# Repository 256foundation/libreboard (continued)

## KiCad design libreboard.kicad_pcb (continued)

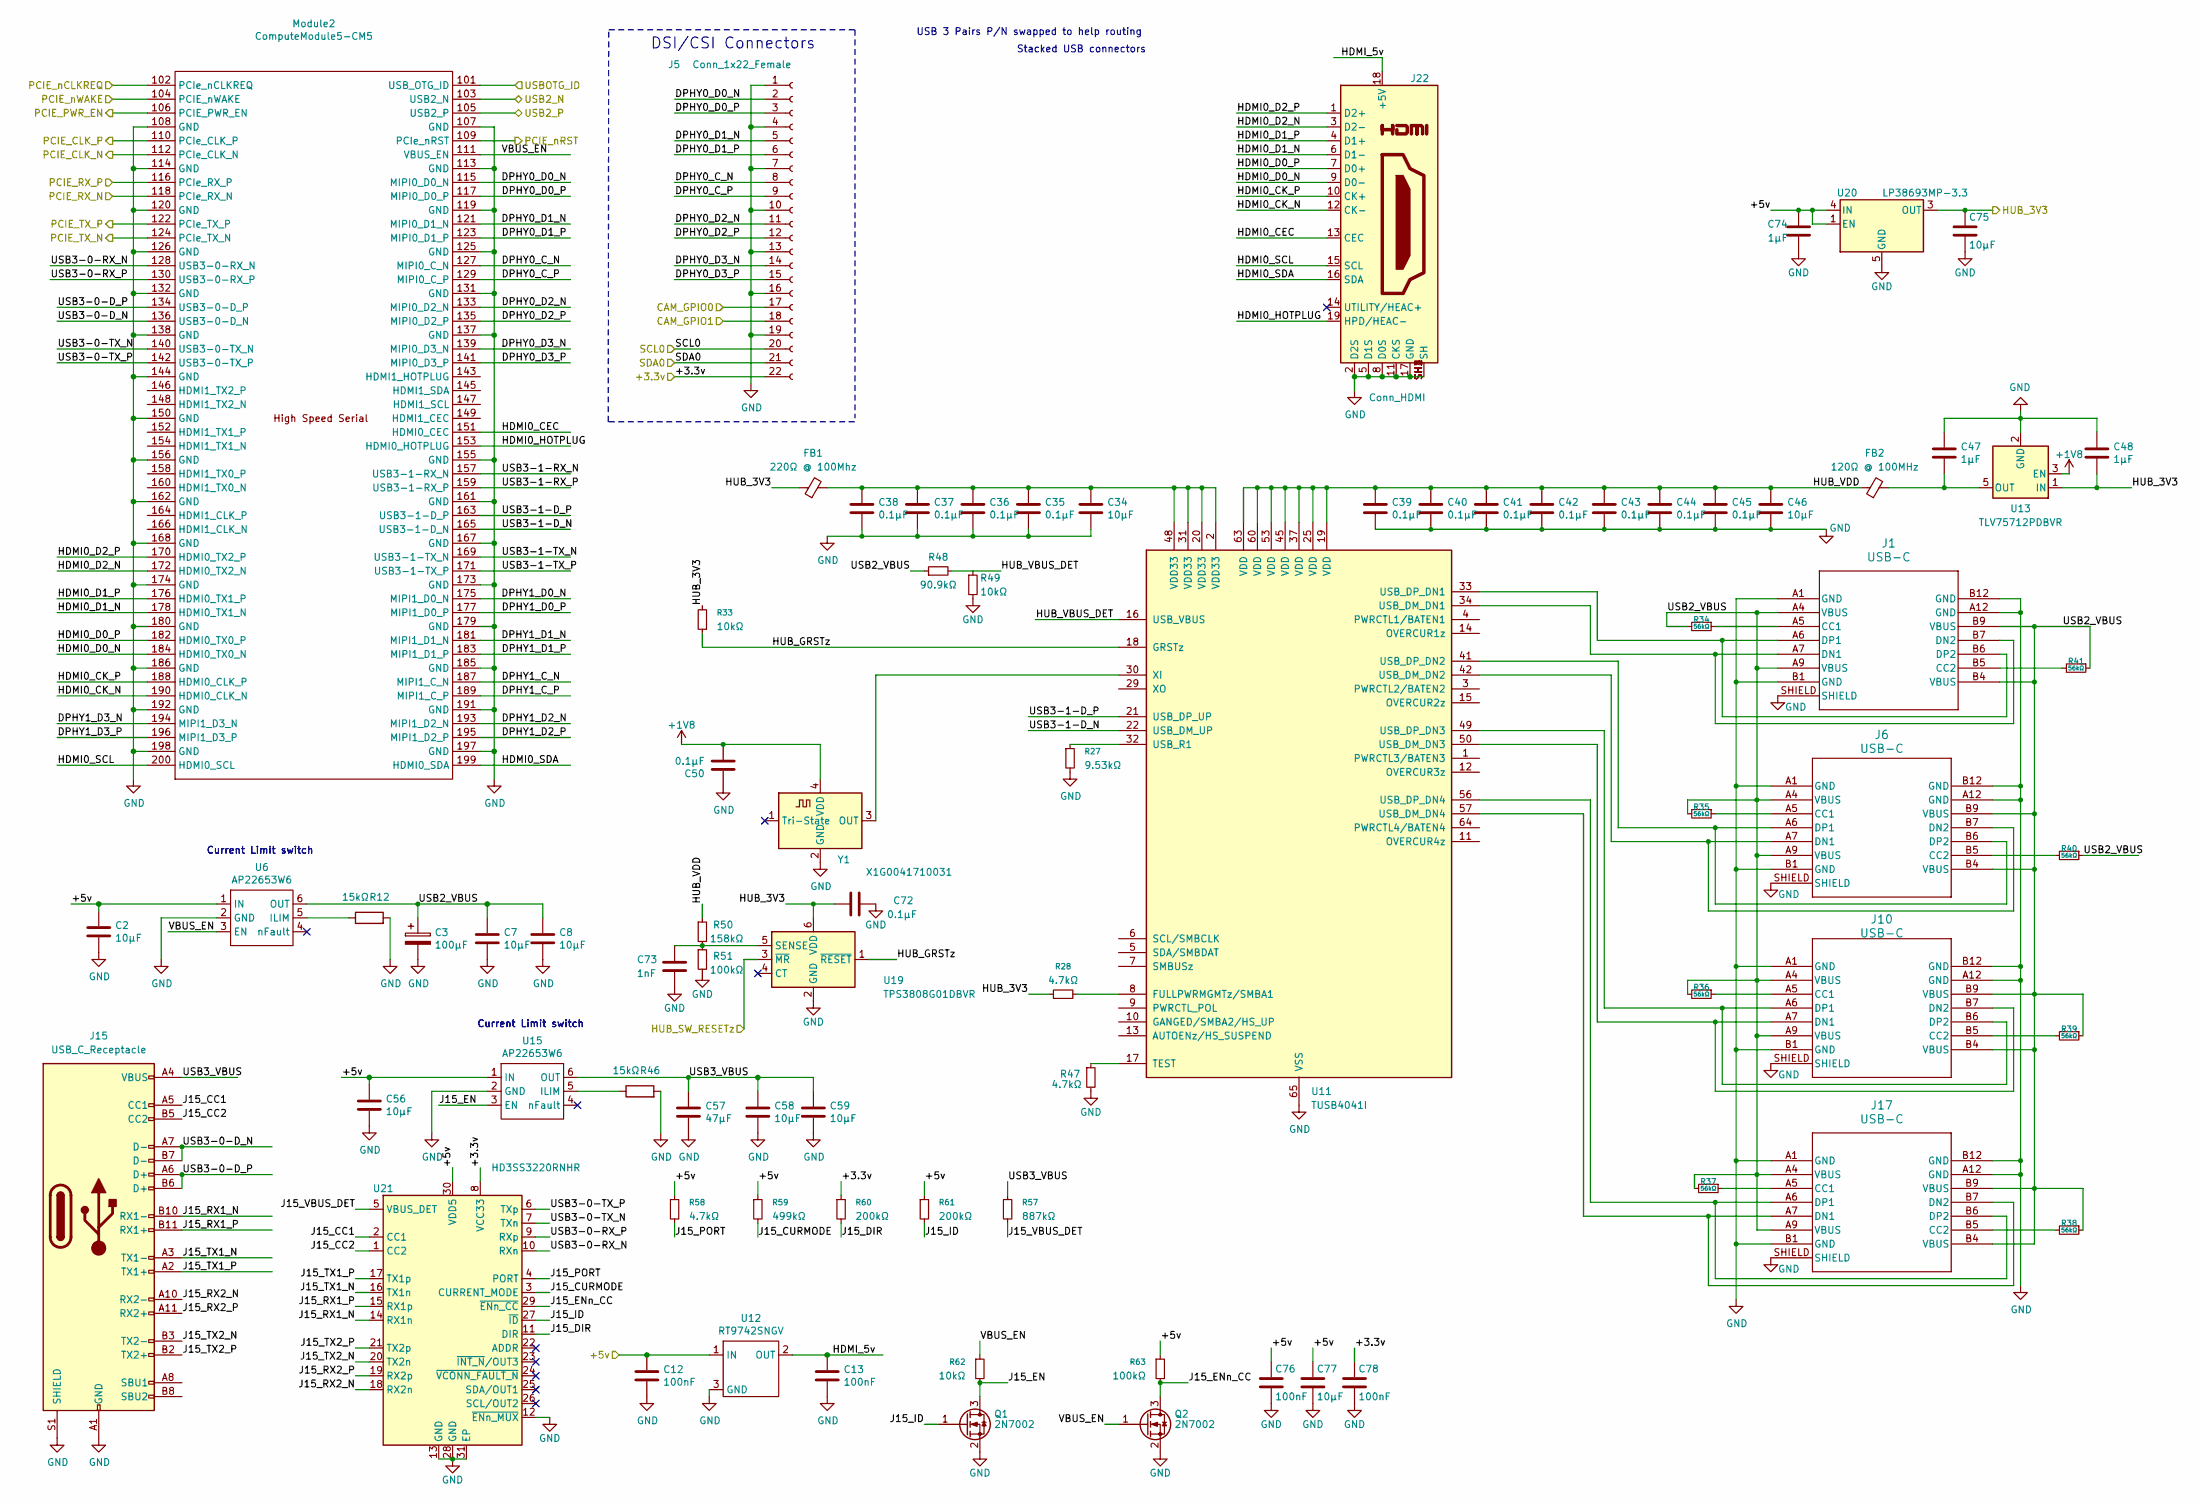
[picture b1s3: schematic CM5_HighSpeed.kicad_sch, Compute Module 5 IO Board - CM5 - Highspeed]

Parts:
C2, C7, C8, C56, C58, C59, C75, C77: 10µF; C_0805_2012Metric; Part Description Capacitor, Ceramic, 10µF, ±10%, 10V, X5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; LCSC C15850
C3: 100µF; CP_EIA-7343-31_Kemet-D; Part Description Capacitor, Aluminum, 100µF, ±20%, 10V, 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; LCSC C3275146
C12, C13: 100nF; C_0402_1005Metric; Part Description Capacitor, Ceramic, 0.1µF, ±10%, 6.3V, 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; LCSC C1525
C34, C46: 10µF; C_0402_1005Metric; Part Description Capacitor, Ceramic, 10µF, ±20%, 6.3V, X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; LCSC C15525
C35, C36, C37, C38, C39, C40, C41, C42, C43, C44, C45, C50: 0.1µF; C_0402_1005Metric; Part Description Capacitor, Ceramic, 0.1µF, ±10%, 6.3V, 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; LCSC C1525
C47, C48: 1µF; C_0402_1005Metric; Part Description Capacitor, Ceramic, 1µF, ±10%, 6.3V, X5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; LCSC C52923
C57: 47µF; C_1206_3216Metric; Part Description 47 µF ±20% 10V Ceramic Capacitor X5R 12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; LCSC C96123
C72: 0.1µF; C_0603_1608Metric; Part Description CAP CER 0.1UF 50V X7R 0603; LCSC C14663
C73: 1nF; C_0603_1608Metric; Part Description Capacitor, Ceramic, 1nF, ±5%, 50V, C0G,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; LCSC C77026
C74: 1µF; C_0402_1005Metric; Part Description 1 µF ±10% 50V Ceramic Capacitor X5R 040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; LCSC C1518208
C76, C78: 100nF; C_0402_1005Metric; Part Description CAP CER 0.1UF 50V X7R 0402; LCSC C307331
FB1: 220Ω @ 100Mhz; BEADC1005X55N; Part Description Filter, Ferrite Bead, 220Ω @ 100MHz, SM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; LCSC C85813
FB2: 120Ω @ 100MHz; L_0603_1608Metric; Part Description Filter, Ferrite Bead, 120Ω @ 100MHz, 3A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; LCSC C85831
J1, J6, J10, J17: USB-C; 216989-0001_MOL; Part Description Receptacle, USB-C, 2.0, 24 pin (14+10 D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; LCSC C3197955
J5: Conn_1x22_Female; Hirose_FH12-22S-0.5SH_1x22-1MP_P0.50mm_Horizontal; Part Description Connector, 22 Position FFC, FPC Connect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; LCSC C597981
J15: USB_C_Receptacle; USB_C_Receptacle_Molex_105450-0101; Part Description Connector, USB-C 3.2 Gen 2; LCSC C134092
J22: Conn_HDMI; EDAC 690-019-298-412; Part Description Connector, HDMI Type A, Female, Right A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; LCSC C5291558
Module2: ComputeModule5-CM5; CM5_Connector_B; Part Description Connector, CM Receptacle, 100 pin, 0.4m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; LCSC C6782225
Q1, Q2: 2N7002; SOT-23; Part Description MOSFET, N-channel, 60V, 115mA, SOT-23; LCSC C8545
R12, R46: 15kΩ; R_0402_1005Metric; Part Description Resistor, 15kΩ, ±1%, 0.1W, SMD 0402 (10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; LCSC C25756
R27: 9.53kΩ; R_0402_1005Metric; Part Description Resistor, 9.53kΩ, ±1%, 0.1W, SMD 0402 (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; LCSC C409938
R28, R58: 4.7kΩ; R_0402_1005Metric; Part Description Resistor, 4.7kΩ, ±1%, 0.1W, SMD 0402 (1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; LCSC C25900
R33, R62: 10kΩ; R_0402_1005Metric; Part Description Resistor, 10kΩ, ±1%, 0.1W, SMD 0402 (10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; LCSC C25744
R34, R35, R36, R37, R38, R39, R40, R41: 56kΩ; R_0402_1005Metric; Part Description Resistor, 56kΩ, ±1%, 0.1W, SMD 0402 (10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; LCSC C25796
R47: 4.7kΩ; R_0603_1608Metric; Part Description Resistor, 4.7kΩ, ±1%, 0.1W, SMD 0603 (1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; LCSC C23162
R48: 90.9kΩ; R_0603_1608Metric; Part Description Resistor, 90.9kΩ, ±1%, 0.1W, SMD 0603 (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; LCSC C403390
R49: 10kΩ; R_0603_1608Metric; Part Description Resistor, 10kΩ, ±1%, 0.1W, SMD 0603 (16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; LCSC C25804
R50: 158kΩ; R_0603_1608Metric; Part Description Resistor, 158kΩ, ±1%, 0.1W, SMD 0603 (1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; LCSC C22883
R51: 100kΩ; R_0603_1608Metric; Part Description Resistor, 100kΩ, ±1%, 0.1W, SMD 0603 (1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; LCSC C25803
R57: 887kΩ; R_0402_1005Metric; Part Description Resistor, 887kΩ, ±1%, 0.1W, SMD 0402 (1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; LCSC C409935
R59: 499kΩ; R_0402_1005Metric; Part Description Resistor, 499kΩ, ±1%, 0.1W, SMD 0402 (1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; LCSC C2986233
R60, R61: 200kΩ; R_0402_1005Metric; Part Description Resistor, 200kΩ, ±1%, 0.1W, SMD 0402 (1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; LCSC C25764
R63: 100kΩ; R_0402_1005Metric; Part Description Resistor, 100kΩ, ±1%, 0.1W, SMD 0402 (1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; LCSC C25741
U6, U15: AP22653W6; SOT-23-6; Part Description Power Switch/Driver, 1:1, P-Channel, 2.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; LCSC C2158037
U11: TUSB4041I; Texas_TQFP-64-1EP_10x10mm_P0.5mm_EP8x8mm_Mask4.44x4.44mm_Th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; Part Description Controller, USB Hub, 64-HTQFP; LCSC C192089
U12: RT9742SNGV; TSOT-23_HandSoldering; Part Description Power Switch/Driver, 1:1, N-Channel, 50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; LCSC C3235509
U13: TLV75712PDBVR; SOT-23-5; Part Description LDO, fixed 1.2 V, 1 A, SOT-23-5; LCSC C1509296
U19: TPS3808G01DBVR; SOT-23-6; Part Description Voltage supervisor, adjustable (0.405 V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; LCSC C19653
U20: LP38693MP-3.3; SOT-223-5; Part Description IC, LDO, 3.3V, 500mA, SOT-223-5, enable; LCSC C130904
U21: HD3SS3220RNHR; Texas_RNH0030A_WQFN-30-1EP_2.5x4.5mm_P0.4mm_EP1.2x3.2mm_The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; Part Description IC, USB Type-C DRP port controller + US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; LCSC C165155
Y1: X1G0041710031; Oscillator_SMD_ECS_2520MV-xxx-xx-4Pin_2.5x2.0mm; Part Description Oscillator SG-210STF, 24MHz, CMOS, 1.6V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; LCSC C70559

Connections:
+1V8: C50.2, U13.3 (EN), Y1.4 (VDD); also elsewhere on the board
+5v: C2.1, C12.1, C56.1, C74.1, C76.1, C77.1, R58.1, R59.1, R61.1, R63.1, U6.1 (IN), U12.1 (IN), U15.1 (IN), U20.1 (EN), U20.4 (IN), U21.30 (VDD5); also elsewhere on the board
/+3.3v: C78.1, J5.22, R60.1, U21.8 (VCC33); also elsewhere on the board
/CM5_GPIO ( Ethernet, GPIO, SDCARD)/CAM_GPIO0: J5.17; also elsewhere on the board
/CM5_GPIO ( Ethernet, GPIO, SDCARD)/CAM_GPIO1: J5.18; also elsewhere on the board
/CM5_GPIO ( Ethernet, GPIO, SDCARD)/HUB_SW_RESETz: U19.3 (~MR); also elsewhere on the board
/CM5_GPIO ( Ethernet, GPIO, SDCARD)/SCL0: J5.20; also elsewhere on the board
/CM5_GPIO ( Ethernet, GPIO, SDCARD)/SDA0: J5.21; also elsewhere on the board
/CM5_GPIO ( Ethernet, GPIO, SDCARD)/USBOTG: Module2.101 (USB_OTG_ID); also elsewhere on the board
/CM5_HighSpeed/DPHY0_C_N: J5.8, Module2.127 (MIPI0_C_N)
/CM5_HighSpeed/DPHY0_C_P: J5.9, Module2.129 (MIPI0_C_P)
/CM5_HighSpeed/DPHY0_D0_N: J5.2, Module2.115 (MIPI0_D0_N)
/CM5_HighSpeed/DPHY0_D0_P: J5.3, Module2.117 (MIPI0_D0_P)
/CM5_HighSpeed/DPHY0_D1_N: J5.5, Module2.121 (MIPI0_D1_N)
/CM5_HighSpeed/DPHY0_D1_P: J5.6, Module2.123 (MIPI0_D1_P)
/CM5_HighSpeed/DPHY0_D2_N: J5.11, Module2.133 (MIPI0_D2_N)
/CM5_HighSpeed/DPHY0_D2_P: J5.12, Module2.135 (MIPI0_D2_P)
/CM5_HighSpeed/DPHY0_D3_N: J5.14, Module2.139 (MIPI0_D3_N)
/CM5_HighSpeed/DPHY0_D3_P: J5.15, Module2.141 (MIPI0_D3_P)
/CM5_HighSpeed/DPHY1_C_N: Module2.187 (MIPI1_C_N)
/CM5_HighSpeed/DPHY1_C_P: Module2.189 (MIPI1_C_P)
/CM5_HighSpeed/DPHY1_D0_N: Module2.175 (MIPI1_D0_N)
/CM5_HighSpeed/DPHY1_D0_P: Module2.177 (MIPI1_D0_P)
/CM5_HighSpeed/DPHY1_D1_N: Module2.181 (MIPI1_D1_N)
/CM5_HighSpeed/DPHY1_D1_P: Module2.183 (MIPI1_D1_P)
/CM5_HighSpeed/DPHY1_D2_N: Module2.193 (MIPI1_D2_N)
/CM5_HighSpeed/DPHY1_D2_P: Module2.195 (MIPI1_D2_P)
/CM5_HighSpeed/DPHY1_D3_N: Module2.194 (MIPI1_D3_N)
/CM5_HighSpeed/DPHY1_D3_P: Module2.196 (MIPI1_D3_P)
/CM5_HighSpeed/HDMI0_CEC: J22.13 (CEC), Module2.151 (HDMI0_CEC)
/CM5_HighSpeed/HDMI0_CK_N: J22.12 (CK-), Module2.190 (HDMI0_CLK_N)
/CM5_HighSpeed/HDMI0_CK_P: J22.10 (CK+), Module2.188 (HDMI0_CLK_P)
/CM5_HighSpeed/HDMI0_D0_N: J22.9 (D0-), Module2.184 (HDMI0_TX0_N)
/CM5_HighSpeed/HDMI0_D0_P: J22.7 (D0+), Module2.182 (HDMI0_TX0_P)
/CM5_HighSpeed/HDMI0_D1_N: J22.6 (D1-), Module2.178 (HDMI0_TX1_N)
/CM5_HighSpeed/HDMI0_D1_P: J22.4 (D1+), Module2.176 (HDMI0_TX1_P)
/CM5_HighSpeed/HDMI0_D2_N: J22.3 (D2-), Module2.172 (HDMI0_TX2_N)
/CM5_HighSpeed/HDMI0_D2_P: J22.1 (D2+), Module2.170 (HDMI0_TX2_P)
/CM5_HighSpeed/HDMI0_HOTPLUG: J22.19 (HPD/HEAC-), Module2.153 (HDMI0_HOTPLUG)
/CM5_HighSpeed/HDMI0_SCL: J22.15 (SCL), Module2.200 (HDMI0_SCL)
/CM5_HighSpeed/HDMI0_SDA: J22.16 (SDA), Module2.199 (HDMI0_SDA)
/CM5_HighSpeed/HDMI_5v: C13.1, J22.18 (+5V), U12.2 (OUT)
/CM5_HighSpeed/HUB_GRSTz: R33.1, U11.18 (GRSTz), U19.1 (~RESET)
/CM5_HighSpeed/HUB_VBUS_DET: R48.2, R49.1, U11.16 (USB_VBUS)
/CM5_HighSpeed/HUB_VDD: C39.1, C40.1, C41.1, C42.1, C43.1, C44.1, C45.1, C46.1, FB2.1, R50.1, U11.19 (VDD), U11.25 (VDD), U11.37 (VDD), U11.45 (VDD), U11.53 (VDD), U11.60 (VDD), U11.63 (VDD)
/CM5_HighSpeed/J15_CC1: J15.A5 (CC1), U21.2 (CC1)
/CM5_HighSpeed/J15_CC2: J15.B5 (CC2), U21.1 (CC2)
/CM5_HighSpeed/J15_CURMODE: R59.2, U21.3 (CURRENT_MODE)
/CM5_HighSpeed/J15_DIR: R60.2, U21.11 (DIR)
/CM5_HighSpeed/J15_EN: Q1.3 (D), R62.2, U15.3 (EN)
/CM5_HighSpeed/J15_ENn_CC: Q2.3 (D), R63.2, U21.29 (~ENn_CC)
/CM5_HighSpeed/J15_ID: Q1.1 (G), R61.2, U21.27 (~ID)
/CM5_HighSpeed/J15_PORT: R58.2, U21.4 (PORT)
/CM5_HighSpeed/J15_RX1_N: J15.B10 (RX1-), U21.14 (RX1n)
/CM5_HighSpeed/J15_RX1_P: J15.B11 (RX1+), U21.15 (RX1p)
/CM5_HighSpeed/J15_RX2_N: J15.A10 (RX2-), U21.18 (RX2n)
/CM5_HighSpeed/J15_RX2_P: J15.A11 (RX2+), U21.19 (RX2p)
/CM5_HighSpeed/J15_TX1_N: J15.A3 (TX1-), U21.16 (TX1n)
/CM5_HighSpeed/J15_TX1_P: J15.A2 (TX1+), U21.17 (TX1p)
/CM5_HighSpeed/J15_TX2_N: J15.B3 (TX2-), U21.20 (TX2n)
/CM5_HighSpeed/J15_TX2_P: J15.B2 (TX2+), U21.21 (TX2p)
/CM5_HighSpeed/J15_VBUS_DET: R57.2, U21.5 (VBUS_DET)
/CM5_HighSpeed/PCIE_CLK_N: Module2.112 (PCIe_CLK_N); also elsewhere on the board
/CM5_HighSpeed/PCIE_CLK_P: Module2.110 (PCIe_CLK_P); also elsewhere on the board
/CM5_HighSpeed/PCIE_PWR_EN: Module2.106 (PCIE_PWR_EN); also elsewhere on the board
/CM5_HighSpeed/PCIE_RX_N: Module2.118 (PCIe_RX_N); also elsewhere on the board
/CM5_HighSpeed/PCIE_RX_P: Module2.116 (PCIe_RX_P); also elsewhere on the board
/CM5_HighSpeed/PCIE_TX_N: Module2.124 (PCIe_TX_N); also elsewhere on the board
/CM5_HighSpeed/PCIE_TX_P: Module2.122 (PCIe_TX_P); also elsewhere on the board
/CM5_HighSpeed/PCIE_nCLKREQ: Module2.102 (PCIe_nCLKREQ); also elsewhere on the board
/CM5_HighSpeed/PCIE_nRST: Module2.109 (PCIe_nRST); also elsewhere on the board
/CM5_HighSpeed/PCIE_nWAKE: Module2.104 (PCIE_nWAKE); also elsewhere on the board
/CM5_HighSpeed/USB2_VBUS: C3.1, C7.1, C8.1, J1.A4 (VBUS), J1.A9 (VBUS), J1.B4 (VBUS), J1.B9 (VBUS), J6.A4 (VBUS), J6.A9 (VBUS), J6.B4 (VBUS), J6.B9 (VBUS), J10.A4 (VBUS), J10.A9 (VBUS), J10.B4 (VBUS), J10.B9 (VBUS), J17.A4 (VBUS), J17.A9 (VBUS), J17.B4 (VBUS), J17.B9 (VBUS), R34.2, R35.2, R36.2, R37.2, R38.1, R39.1, R40.1, R41.1, R48.1, U6.6 (OUT)
/CM5_HighSpeed/USB3-0-D_N: J15.A7 (D-), J15.B7 (D-), Module2.136 (USB3-0-D_N)
/CM5_HighSpeed/USB3-0-D_P: J15.A6 (D+), J15.B6 (D+), Module2.134 (USB3-0-D_P)
/CM5_HighSpeed/USB3-0-RX_N: Module2.128 (USB3-0-RX_N), U21.10 (RXn)
/CM5_HighSpeed/USB3-0-RX_P: Module2.130 (USB3-0-RX_P), U21.9 (RXp)
/CM5_HighSpeed/USB3-0-TX_N: Module2.140 (USB3-0-TX_N), U21.7 (TXn)
/CM5_HighSpeed/USB3-0-TX_P: Module2.142 (USB3-0-TX_P), U21.6 (TXp)
/CM5_HighSpeed/USB3-1-D_N: Module2.165 (USB3-1-D_N), U11.22 (USB_DM_UP)
/CM5_HighSpeed/USB3-1-D_P: Module2.163 (USB3-1-D_P), U11.21 (USB_DP_UP)
/CM5_HighSpeed/USB3-1-RX_N: Module2.157 (USB3-1-RX_N)
/CM5_HighSpeed/USB3-1-RX_P: Module2.159 (USB3-1-RX_P)
/CM5_HighSpeed/USB3-1-TX_N: Module2.169 (USB3-1-TX_N)
/CM5_HighSpeed/USB3-1-TX_P: Module2.171 (USB3-1-TX_P)
/CM5_HighSpeed/USB3_VBUS: C57.1, C58.1, C59.1, J15.A4 (VBUS), J15.A9 (VBUS), J15.B4 (VBUS), J15.B9 (VBUS), R57.1, U15.6 (OUT)
/CM5_HighSpeed/VBUS_EN: Module2.111 (VBUS_EN), Q2.1 (G), R62.1, U6.3 (EN)
/HUB_3V3: C48.2, C72.1, C75.1, FB1.1, R28.1, R33.2, U13.1 (IN), U19.6 (VDD), U20.3 (OUT); also elsewhere on the board
/USB2_N: Module2.103 (USB2_N); also elsewhere on the board
/USB2_P: Module2.105 (USB2_P); also elsewhere on the board
GND: C2.2, C3.2, C7.2, C8.2, C12.2, C13.2, C34.2, C35.2, C36.2, C37.2, C38.2, C39.2, C40.2, C41.2, C42.2, C43.2, C44.2, C45.2, C46.2, C47.1, C48.1, C50.1, C56.2, C57.2, C58.2, C59.2, C72.2, C73.2, C74.2, C75.2, C76.2, C77.2, C78.2, J1.A1 (GND), J1.A12 (GND), J1.B1 (GND), J1.B12 (GND), J1.SHIELD, J5.1, J5.4, J5.7, J5.10, J5.13, J5.16, J5.19, J6.A1 (GND), J6.A12 (GND), J6.B1 (GND), J6.B12 (GND), J6.SHIELD, J10.A1 (GND), J10.A12 (GND), J10.B1 (GND), J10.B12 (GND), J10.SHIELD, J15.A1 (GND), J15.A12 (GND), J15.B1 (GND), J15.B12 (GND), J15.S1 (SHIELD), J17.A1 (GND), J17.A12 (GND), J17.B1 (GND), J17.B12 (GND), J17.SHIELD, J22.2 (D2S), J22.5 (D1S), J22.8 (D0S), J22.11 (CKS), J22.17 (GND), J22.SH1 (SH), J22.SH2 (SH), J22.SH3 (SH), J22.SH4 (SH), Module2.107 (GND), Module2.108 (GND), Module2.113 (GND), Module2.114 (GND), Module2.119 (GND), Module2.120 (GND), Module2.125 (GND), Module2.126 (GND), Module2.131 (GND), Module2.132 (GND), Module2.137 (GND), Module2.138 (GND), Module2.144 (GND), Module2.150 (GND), Module2.155 (GND), Module2.156 (GND), Module2.161 (GND), Module2.162 (GND), Module2.167 (GND), Module2.168 (GND), Module2.173 (GND), Module2.174 (GND), Module2.179 (GND), Module2.180 (GND), Module2.185 (GND), Module2.186 (GND), Module2.191 (GND), Module2.192 (GND), Module2.197 (GND), Module2.198 (GND), Q1.2 (S), Q2.2 (S), R12.2, R27.2, R46.2, R47.2, R49.2, R51.2, U6.2 (GND), U11.65 (VSS), U12.3 (GND), U13.2 (GND), U15.2 (GND), U19.2 (GND), U20.5 (GND), U21.12 (~ENn_MUX), U21.13 (GND), U21.28 (GND), U21.31 (EP), Y1.2 (GND); also elsewhere on the board
unnamed: C34.1, C35.1, C36.1, C37.1, C38.1, FB1.2, U11.2 (VDD33), U11.20 (VDD33), U11.31 (VDD33), U11.48 (VDD33)
unnamed: J1.A5 (CC1), R34.1
unnamed: J1.B5 (CC2), R41.2
unnamed: J1.A7 (DN1), J1.B7 (DN2), U11.34 (USB_DM_DN1)
unnamed: J1.A6 (DP1), J1.B6 (DP2), U11.33 (USB_DP_DN1)
unnamed: J6.A5 (CC1), R35.1
unnamed: J6.B5 (CC2), R40.2
unnamed: J6.A7 (DN1), J6.B7 (DN2), U11.42 (USB_DM_DN2)
unnamed: J6.A6 (DP1), J6.B6 (DP2), U11.41 (USB_DP_DN2)
unnamed: J10.A5 (CC1), R36.1
unnamed: J10.B5 (CC2), R39.2
unnamed: J10.A7 (DN1), J10.B7 (DN2), U11.50 (USB_DM_DN3)
unnamed: J10.A6 (DP1), J10.B6 (DP2), U11.49 (USB_DP_DN3)
unnamed: J17.A5 (CC1), R37.1
unnamed: J17.B5 (CC2), R38.2
unnamed: J17.A7 (DN1), J17.B7 (DN2), U11.57 (USB_DM_DN4)
unnamed: J17.A6 (DP1), J17.B6 (DP2), U11.56 (USB_DP_DN4)
unnamed: R12.1, U6.5 (ILIM)
unnamed: R28.2, U11.8 (FULLPWRMGMTz/SMBA1)
unnamed: R47.1, U11.17 (TEST)
unnamed: R27.1, U11.32 (USB_R1)
unnamed: U11.30 (XI), Y1.3 (OUT)
unnamed: C47.2, FB2.2, U13.5 (OUT)
unnamed: R46.1, U15.5 (ILIM)
unnamed: C73.1, R50.2, R51.1, U19.5 (SENSE)

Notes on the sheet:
USB 3 Pairs P/N swapped to help routing
Current Limit switch
DSI/CSI Connectors
Stacked USB connectors

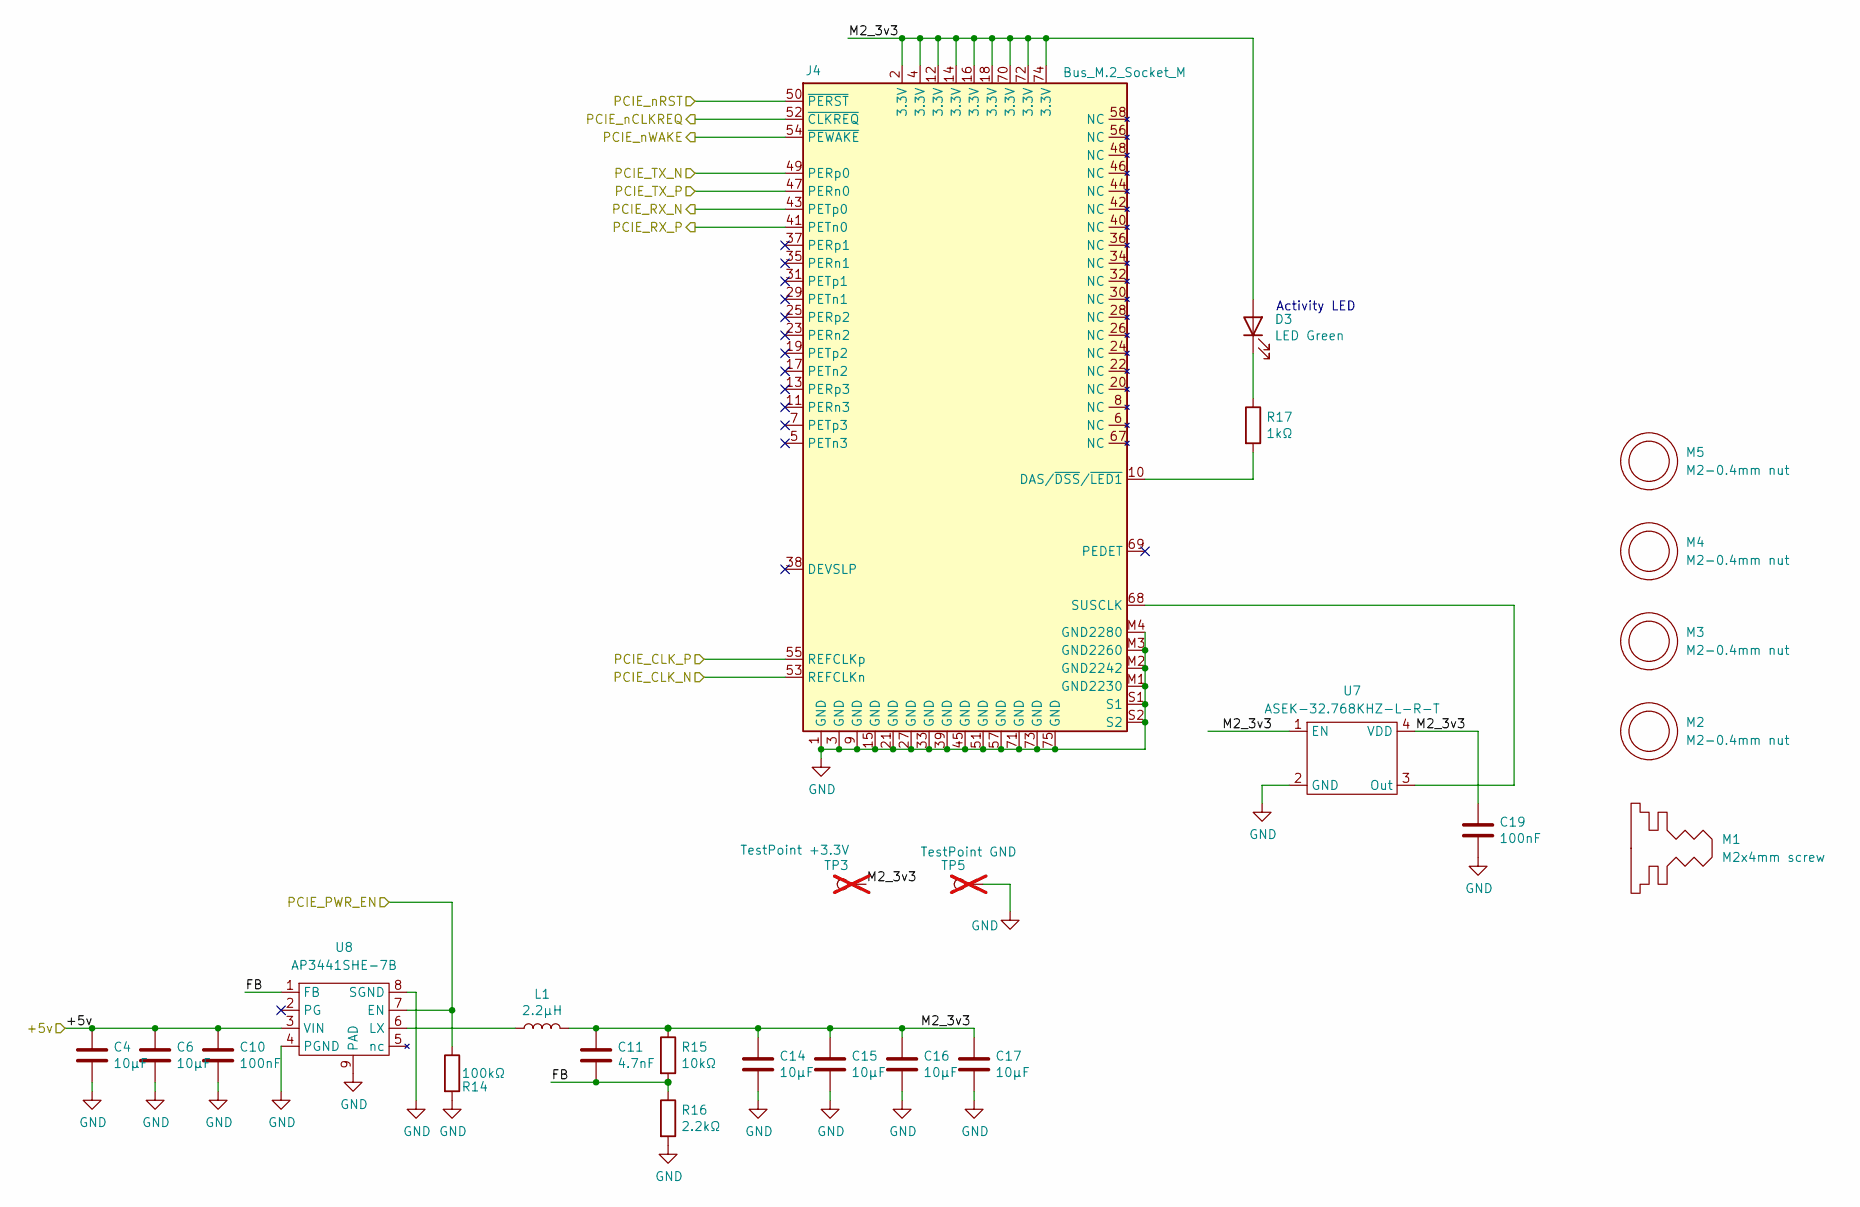
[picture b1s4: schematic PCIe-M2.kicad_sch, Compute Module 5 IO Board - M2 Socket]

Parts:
C4, C6, C14, C15, C16, C17: 10µF; C_0805_2012Metric; Part Description Capacitor, Ceramic, 10µF, ±10%, 10V, X5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; LCSC C15850
C10, C19: 100nF; C_0402_1005Metric; Part Description Capacitor, Ceramic, 0.1µF, ±10%, 6.3V, 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; LCSC C1525
C11: 4.7nF; C_0402_1005Metric; Part Description Capacitor, Ceramic, 4700pF, ±10%, 10V, 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; LCSC C1538
D3: LED Green; LED_0603_1608Metric; Part Description LED, Green, 572nm, 2.2V, SMD 0603; LCSC C125113
J4: Bus_M.2_Socket_M; M.2 M Key socket; Part Description Connector, M.2, M-Key, 67 pin, 0.5mm P,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; LCSC C574849
L1: 2.2µH; L_Bourns_SRP5030CC; Part Description Inductor, 2.2µH, ±20%, 7A, 32Ω; LCSC C22404330
M1: M2x4mm screw; Part Description PHCS, M2-0.4 x 4mm, Phillips, Stainless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
M2, M3, M4, M5: M2-0.4mm nut; Part Description Standoff, M2 thread, 1.5mm H, 5.56mm Di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; LCSC C2916320
R14: 100kΩ; R_0402_1005Metric; Part Description Resistor, 100kΩ, ±1%, 0.1W, SMD 0402 (1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; LCSC C25741
R15: 10kΩ; R_0402_1005Metric; Part Description Resistor, 10kΩ, ±1%, 0.1W, SMD 0402 (10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; LCSC C25744
R16: 2.2kΩ; R_0402_1005Metric; Part Description Resistor, 2.2kΩ, ±1%, 0.1W, SMD 0402 (1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; LCSC C25879
R17: 1kΩ; R_0402_1005Metric; Part Description Resistor, 1kΩ, ±1%, 0.1W, SMD 0402 (100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; LCSC C11702
TP3: TestPoint +3.3V; TestPoint_Pad_D1.5mm; Part Description Test point; not fitted
TP5: TestPoint GND; TestPoint_Pad_D1.5mm; Part Description Test point; not fitted
U7: ASEK-32.768KHZ-L-R-T; Crystal_SMD_3225-4Pin_3.2x2.5mm; Part Description Oscillator, 32.768kHz, 3.3V; LCSC C2650753
U8: AP3441SHE-7B; DFN-8-1EP_2x2mm_P0.5mm_EP1.05x1.75mm; Part Description Buck Converter, 0.6V, 3A; LCSC C2070918

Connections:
+5v: C4.1, C6.1, C10.1, U8.3 (VIN); also elsewhere on the board
/CM5_HighSpeed/PCIE_CLK_N: J4.53 (REFCLKn); also elsewhere on the board
/CM5_HighSpeed/PCIE_CLK_P: J4.55 (REFCLKp); also elsewhere on the board
/CM5_HighSpeed/PCIE_PWR_EN: R14.1, U8.7 (EN); also elsewhere on the board
/CM5_HighSpeed/PCIE_RX_N: J4.43 (PETp0); also elsewhere on the board
/CM5_HighSpeed/PCIE_RX_P: J4.41 (PETn0); also elsewhere on the board
/CM5_HighSpeed/PCIE_TX_N: J4.49 (PERp0); also elsewhere on the board
/CM5_HighSpeed/PCIE_TX_P: J4.47 (PERn0); also elsewhere on the board
/CM5_HighSpeed/PCIE_nCLKREQ: J4.52 (~CLKREQ); also elsewhere on the board
/CM5_HighSpeed/PCIE_nRST: J4.50 (~PERST); also elsewhere on the board
/CM5_HighSpeed/PCIE_nWAKE: J4.54 (~PEWAKE); also elsewhere on the board
/PCIe-M2/FB: C11.2, R15.2, R16.1, U8.1 (FB)
/PCIe-M2/M2_3v3: C11.1, C14.1, C15.1, C16.1, C17.1, C19.1, D3.2 (A), J4.2 (3.3V), J4.4 (3.3V), J4.12 (3.3V), J4.14 (3.3V), J4.16 (3.3V), J4.18 (3.3V), J4.70 (3.3V), J4.72 (3.3V), J4.74 (3.3V), L1.2, R15.1, TP3.1 (1_1), U7.1 (EN), U7.4 (VDD)
GND: C4.2, C6.2, C10.2, C14.2, C15.2, C16.2, C17.2, C19.2, J4.1 (GND), J4.3 (GND), J4.9 (GND), J4.15 (GND), J4.21 (GND), J4.27 (GND), J4.33 (GND), J4.39 (GND), J4.45 (GND), J4.51 (GND), J4.57 (GND), J4.71 (GND), J4.73 (GND), J4.75 (GND), J4.M1 (GND2230), J4.M2 (GND2242), J4.M3 (GND2260), J4.M4 (GND2280), J4.S1, J4.S2, R14.2, R16.2, TP5.1 (1_1), U7.2 (GND), U8.4 (PGND), U8.8 (SGND), U8.9 (PAD); also elsewhere on the board
unnamed: D3.1 (K), R17.1
unnamed: J4.10 (DAS/~DSS/~LED1), R17.2
unnamed: J4.68 (SUSCLK), U7.3 (Out)
unnamed: L1.1, U8.6 (LX)

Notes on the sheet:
Activity LED

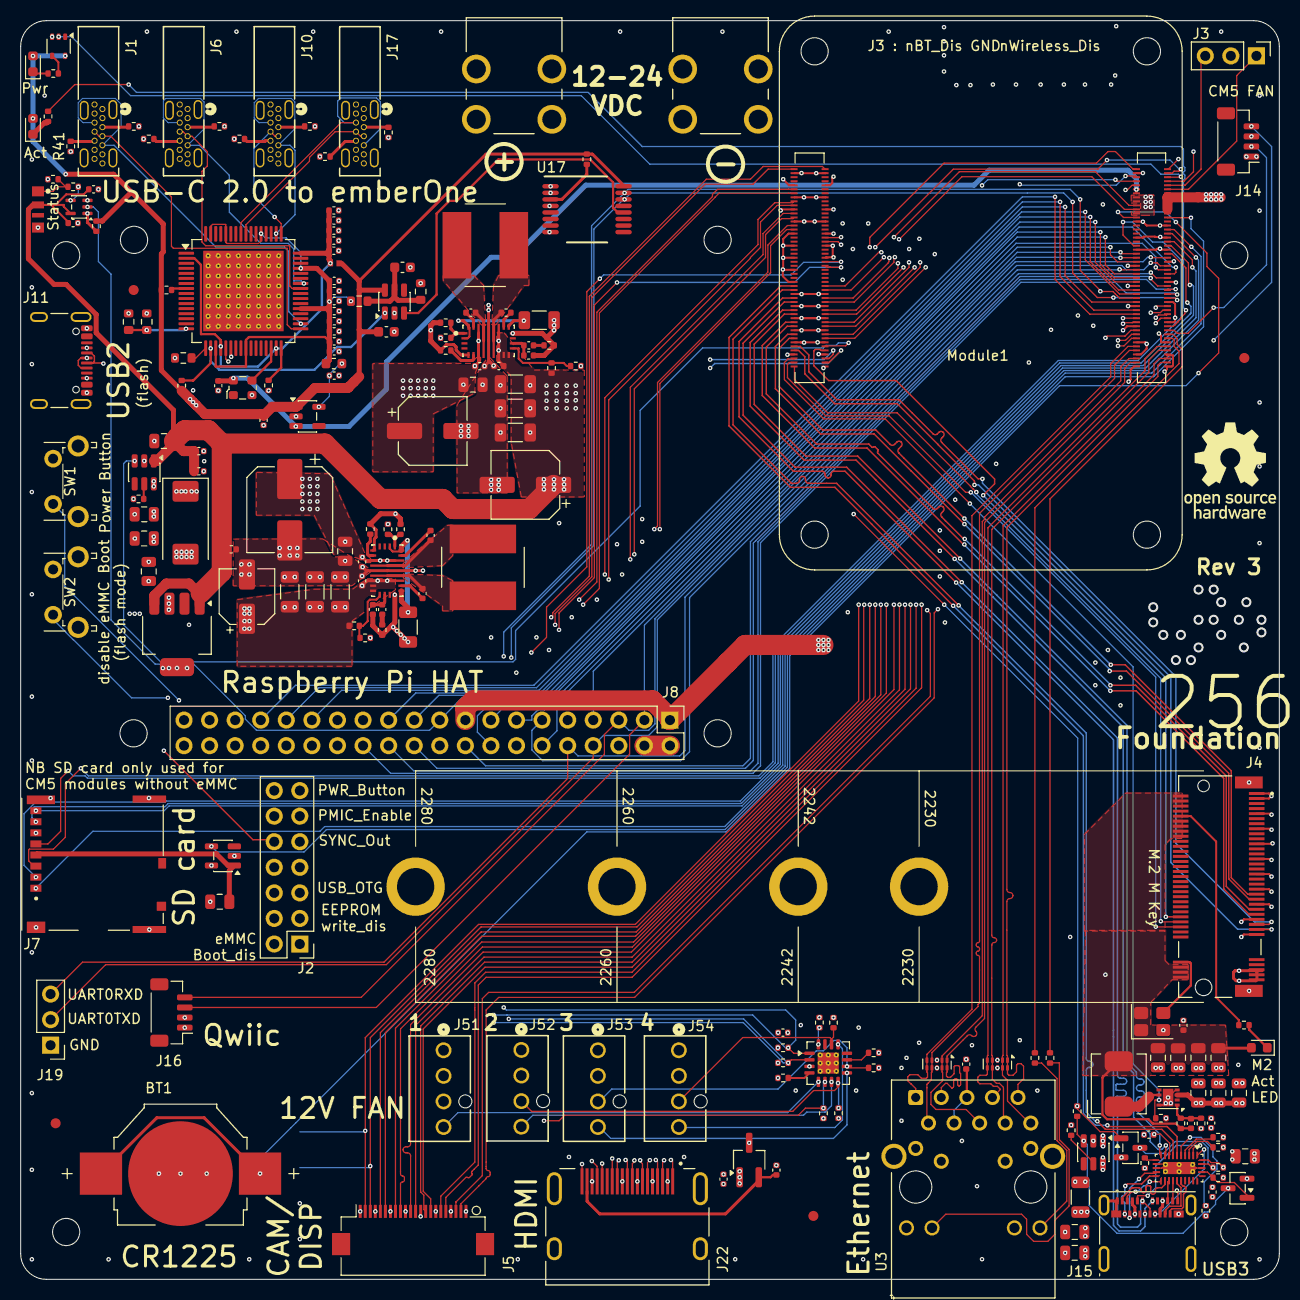
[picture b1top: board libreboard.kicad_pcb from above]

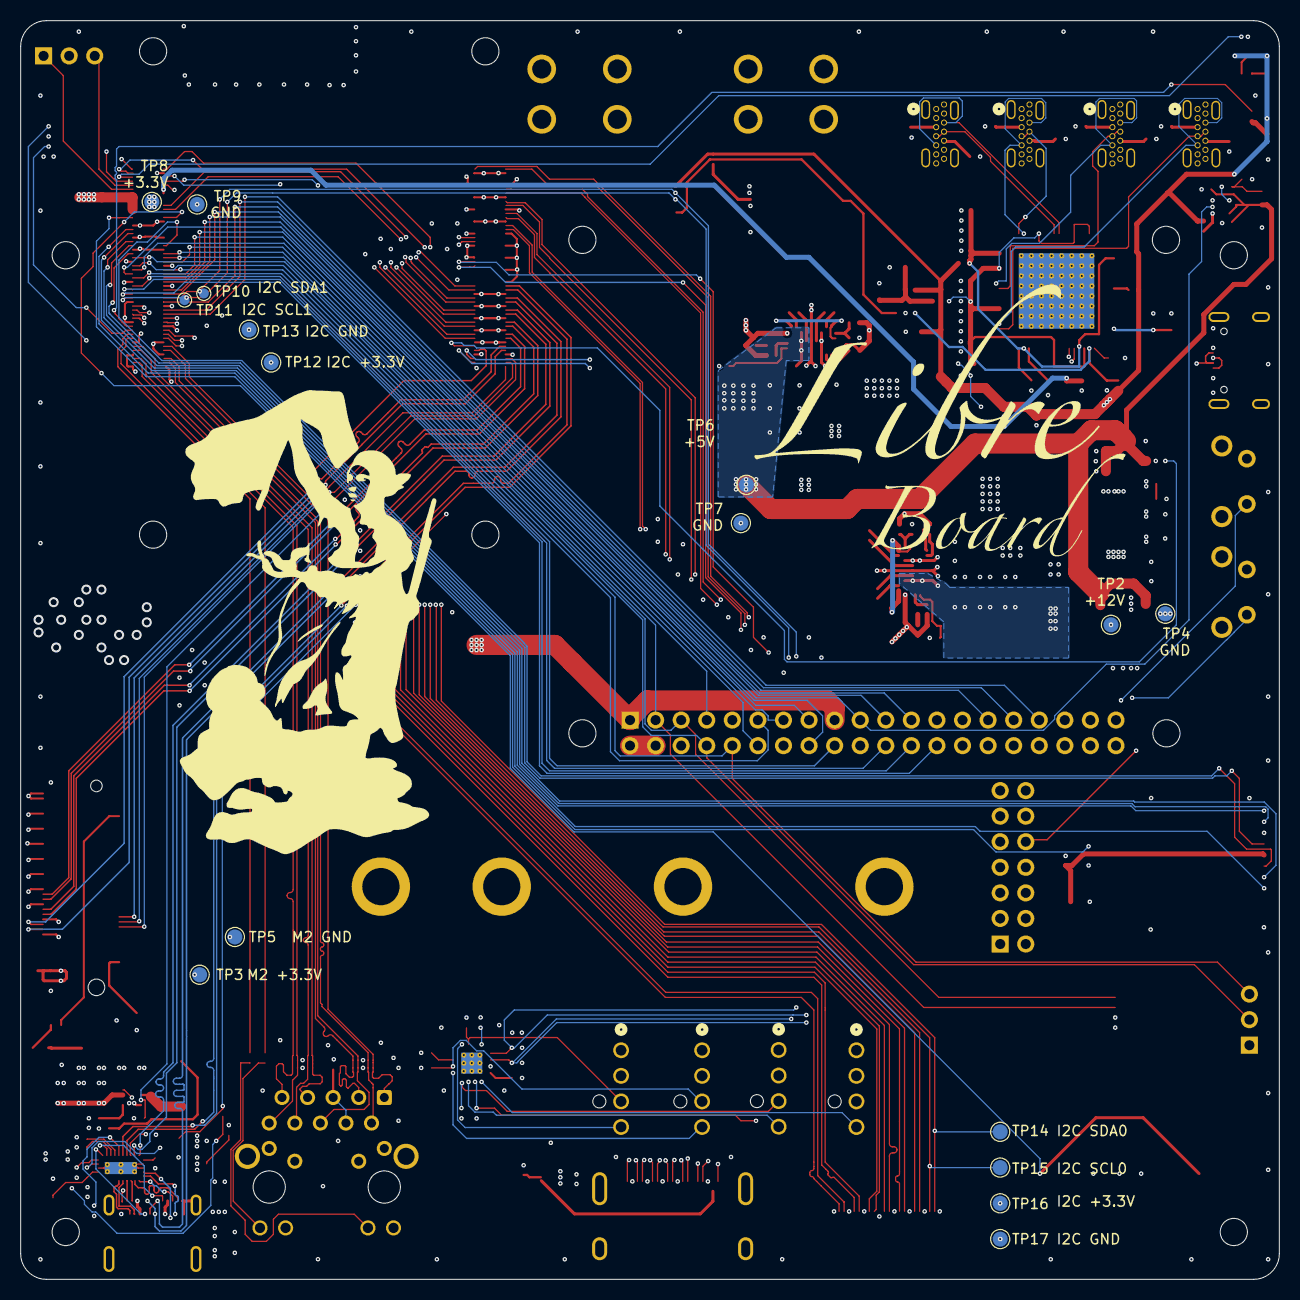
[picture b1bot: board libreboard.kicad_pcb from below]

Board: 6 copper layers, 125.0 x 125.0 mm, 220 parts (16 on the bottom side), 211 nets.

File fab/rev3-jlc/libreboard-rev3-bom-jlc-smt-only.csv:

Comment,Designator,Footprint,LCSC Part #
Battery_Cell,BT1,BAT_BAT-HLD-007-SMT-TR,C6997853
0.1uF,"C1,C9,C10,C12,C13,C18,C19,C31,C35,C36,C37,C38,C39,C40,C41,C42,C43,C44,C45,C50,C70",C_0402_1005Metric,C1525
10uF,"C2,C4,C5,C6,C7,C8,C14,C15,C16,C17,C56,C58,C59,C75,C77",C_0805_2012Metric,C15850
100uF,C3,CP_EIA-7343-31_Kemet-D,C3275146
4.7nF,C11,C_0402_1005Metric,C1538
39uF,C20,CP_Elec_8x6.7,C7059708
10uF,"C21,C52",C_0805_2012Metric,C440198
1uF,"C22,C30,C54,C74",C_0402_1005Metric,C1518208
4.7uF,"C23,C53",C_1206_3216Metric,C29823
100nF,"C24,C25,C55,C65,C76,C78",C_0402_1005Metric,C307331
33uF,"C27,C28,C29",C_1206_3216Metric,C342307
10uF,"C34,C46",C_0402_1005Metric,C15525
1uF,"C47,C48,C64",C_0402_1005Metric,C52923
22uF,C51,CP_Elec_6.3x5.9,C46550474
47uF,"C57,C66,C67,C68",C_1206_3216Metric,C96123
6.8pF,C60,C_0402_1005Metric,C1576
1nF,C61,C_0402_1005Metric,C76947
2.2nF,C62,C_0402_1005Metric,C1531
3.9pF,C63,C_0402_1005Metric,C1517504
270uF,C69,CP_Elec_6.3x9.9,C2944013
10uF,C71,C_0402_1005Metric,C408132
0.1uF,C72,C_0603_1608Metric,C14663
1nF,C73,C_0603_1608Metric,C77026
LED Red,D1,LED_0603_1608Metric,C125114
LED Green,"D2,D3",LED_0603_1608Metric,C125113
220 @ 100Mhz,FB1,BEADC1005X55N,C85813
120 @ 100MHz,FB2,L_0603_1608Metric,C85831
Bus_M.2_Socket_M,J4,M.2 M Key socket,C574849
Conn_1x22_Female,J5,Hirose_FH12-22S-0.5SH_1x22-1MP_P0.50mm_Horizontal,C597981
Micro_SD_Card_Det,J7,SDCARD_MOLEX_503398-1892,C428492
USB_C_Receptacle_USB2.0,J11,USB_C_Receptacle_GCT_USB4105-xx-A_16P_TopMnt_Horizontal,C5184243
JST_BM04B-SRSS-TB,"J14,J16",JST_SH_BM04B-SRSS-TB_1x04-1MP_P1.00mm_Vertical,C160390
USB_C_Receptacle,J15,USB_C_Receptacle_Molex_105450-0101,C134092
Conn_HDMI,J22,EDAC 690-019-298-412,C5291558
2.2uH,L1,L_Bourns_SRP5030CC,C22404330
4.7uH,"L2,L3",L_Bourns_SRN8040TA,C6685196
ComputeModule5-CM5,"Module1,Module2",CM5_Connector_A / CM5_Connector_B,C6782225
2N7002,"Q1,Q2",SOT-23,C8545
1k,"R1,R10,R17",R_0402_1005Metric,C11702
470,"R2,R3,R9",R_0402_1005Metric,C25117
10k,"R4,R15,R21,R22,R23,R24,R29,R30,R33,R52,R62,R64",R_0402_1005Metric,C25744
301k,"R6,R18",R_0402_1005Metric,C7209900
45.3k,"R7,R19",R_0402_1005Metric,C2986582
48.7k,R8,R_0402_1005Metric,C2077134
60.4k,R11,R_0402_1005Metric,C2986234
15k,"R12,R46",R_0402_1005Metric,C25756
50k,R13,R_0402_1005Metric,C7501196
100k,"R14,R42,R53,R55,R63",R_0402_1005Metric,C25741
2.2k,R16,R_0402_1005Metric,C25879
25.5k,R20,R_0402_1005Metric,C2076811
9.53k,R27,R_0402_1005Metric,C409938
4.7k,"R28,R58",R_0402_1005Metric,C25900
22k,R31,R_0402_1005Metric,C25768
33k,R32,R_0402_1005Metric,C25779
56k,"R34,R35,R36,R37,R38,R39,R40,R41",R_0402_1005Metric,C25796
4.7k,R47,R_0603_1608Metric,C23162
90.9k,R48,R_0603_1608Metric,C403390
10k,R49,R_0603_1608Metric,C25804
158k,R50,R_0603_1608Metric,C22883
100k,R51,R_0603_1608Metric,C25803
30.1k,R54,R_0402_1005Metric,C2076806
11.0k,R56,R_0402_1005Metric,C409880
887k,R57,R_0402_1005Metric,C409935
499k,R59,R_0402_1005Metric,C2986233
200k,"R60,R61",R_0402_1005Metric,C25764
TPS552892QWRYQRQ1,"U4,U14",RYQ0021A-MFG,C22375748
74LVC1G07SE-7,U5,SOT-353_SC-70-5,C67531
AP22653W6,"U6,U15",SOT-23-6,C2158037
ASEK-32.768KHZ-L-R-T,U7,Crystal_SMD_3225-4Pin_3.2x2.5mm,C2650753
AP3441SHE-7B,U8,DFN-8-1EP_2x2mm_P0.5mm_EP1.05x1.75mm,C2070918
SK6812,U9,LED-SMD_4P-L4.0-W1.6-L,C2890037
EMC2305-x-AP,U10,Texas_RGV0016A_VQFN-16-1EP_4x4mm_P0.65mm_EP2.1x2.1mm_ThermalVias,C621415
TUSB4041I,U11,Texas_TQFP-64-1EP_10x10mm_P0.5mm_EP8x8mm_Mask4.44x4.44mm_ThermalVias,C192089
RT9742SNGV,U12,TSOT-23_HandSoldering,C3235509
TLV75712PDBVR,U13,SOT-23-5,C1509296
SN74AHCT1G125DCKR,U16,SOT-353_SC-70-5,C350557
RT9742GGJ5,U18,SOT-23-5,C250547
TPS3808G01DBVR,U19,SOT-23-6,C19653
LP38693MP-3.3,U20,SOT-223-5,C130904
HD3SS3220RNHR,U21,Texas_RNH0030A_WQFN-30-1EP_2.5x4.5mm_P0.4mm_EP1.2x3.2mm_ThermalVias,C165155
X1G0041710031,Y1,Oscillator_SMD_ECS_2520MV-xxx-xx-4Pin_2.5x2.0mm,C70559

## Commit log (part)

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2025-08-20 starting to trace
2025-08-25 fully traced
2025-08-29 small tracing fixes
2025-08-30 update BOM
2025-09-12 voltage regulator refactoring
2025-09-15 place all components
2025-09-17 update BOM
    Author: econoalchemist
    modified: CM5_GPIO.kicad_sch
    modified: CM5_HighSpeed.kicad_sch
    modified: PCIe-M2.kicad_sch
    modified: libreboard.kicad_pcb
    modified: libreboard.kicad_pro
2025-09-17 modified: libreboard.kicad_pro libreboard.csv
2025-09-17 updates BOM, sychronizes PCB from schematic, & includes error report.
2025-09-18 change C27-C29 to 1206, reroute i2c
2025-09-19 C27-C29 update
2025-09-23 cleanup, testpoints
2025-09-24 fix all DRC issues
2025-09-25 final review, added coincell back, additional testpoints, updated i2c bus for quic
2025-09-29 updating traces: min 1.3mm width, diff pairs lengths
2025-10-03 Update README and replace images: removed outdated edge views and top face view, added new front and back images of the Libre Board.
2025-10-03 Update thickness of traces, smaller fixes
2025-11-14 Rev1
2025-11-14 switch places of C52/C54 and C21/C22 - in order for easier compatbility with Rev2
2025-11-14 switch C21 and C52 to 50V, 0805 size and reposition; Rev2 text
